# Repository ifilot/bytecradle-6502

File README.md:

# ByteCradle 6502

The **ByteCradle 6502** is a **single-board computer (SBC)** platform designed
for understanding and experimenting with **simple operating systems** on **8-bit
hardware**. Built around the **WDC 65C02** microprocessor, it provides a
hands-on platform for studying **system initialization, memory management,
device interfacing, and file system handling**.

> [!NOTE]  
> The source code for the ByteCradle 6502 operating system for the Mini is found
> in [a separate repository](https://github.com/ifilot/bytecradle-6502-operating-system).

## 📋 Table of Contents

- [BYTECRADLE 6502](#bytecradle-6502)
- [Overview](#overview)
  - [Shared Components](#shared-components)
- [Tier Comparison](#tier-comparison)
- [Obtaining PCBs](#obtaining-pcbs)
- [Download ROMs](#download-roms)
- [License](#license)
  - [Software](#software)
  - [Hardware](#hardware)
- [Contributing](#contributing)
- [Acknowledgements](#acknowledgements)

## Overview

Both SBCs share a common design philosophy — to provide a straightforward and
accessible 65C02 system, while exploring different levels of hardware
capability.

### Shared Components

- **CPU**: WDC 65C02
- **I/O**: WDC 65C51 Asynchronous Communications Interface Adapter (ACIA)

## Tier Comparison

This project offers two tiers of single board computers (SBCs), each tailored to
different levels of complexity and expandability:

- **Tiny SBC** (top): A simple, compact design ideal for learning or small
  embedded projects.
- **Mini SBC** (bottom): A more capable version with bank switching, SD card
  storage, and an expansion bus using the 65C22 Versatile Interface Adapter
  (VIA).

| Feature              | Tiny SBC                          | Mini SBC                             |
|----------------------|-----------------------------------|--------------------------------------|
| **PCB**              | Two layer                         | Four layer                           |
| **RAM**              | 32 KiB                            | 512 KiB (bank switched)              |
| **ROM**              | 32 KiB                            | 512 KiB (bank switched)              |
| **Bank Switching**   | No                                | Yes - 64 x 8 Kib banks               |
| **SD Card Support**  | No                                | Yes - Using WDC 65C22 VIA            |
| **I/O Interface**    | WDC 65C51 ACIA                    | WDC 65C51 ACIA                       |
| **Expansion Options**| Exposes system bus                | Exposes system bus and VIA bus       |

## Obtaining PCBs

You can have the ByteCradle PCBs manufactured at any PCB fabrication service of
your choice. However, for convenience and ease of ordering, we recommend using
[PCBWay](https://www.pcbway.com).

The following links will take you directly to the shared projects on PCBWay, where you can order the boards:

- [Order the Mini Board from PCBWay](https://www.pcbway.com/project/shareproject/ByteCradle_6502_Mini_Board_becc5f96.html)
- [Order the Tiny Board from PCBWay](https://www.pcbway.com/project/shareproject/ByteCradle_6502_Tiny_Board_7606b02a.html)

> [!NOTE]  
> These links direct you to the official project pages for the Mini and Tiny
> Boards on PCBWay.

## Download ROMs

Below are the available ROM images for use with the ByteCradle single-board
computers. These ROMs can be flashed onto your device depending on the board you
are using.

- **[TinyROM](https://github.com/ifilot/bytecradle-6502/releases/download/tinyrom-latest/tinyrom.bin)**  
  A lightweight ROM designed specifically for the Tiny Board. Ideal for minimal
  setups, testing, or basic 6502 development.

> [!IMPORTANT]  
> Make sure to select the appropriate ROM for your board model. Flashing the
> incorrect ROM may result in system instability.

## License

### Software

All software (including ROM code, tools, and firmware) in this repository is
licensed under the [GNU General Public License v3.0](LICENSE-GPL).

This means:
- You are free to use, modify, and share the software.
- If you distribute modified versions, you must also release them under the GPLv3.

### Hardware

All hardware design files (schematics, PCB layouts, bills of materials, etc.)
are licensed under the [CERN Open Hardware License v2 - Weakly Reciprocal
(CERN-OHL-W)](LICENSE-HARDWARE).

This means:
- You may study, modify, manufacture, and distribute the hardware freely.
- If you distribute a modified version, you must share your changes under the
  same license.

## Contributing

Contributions, ideas, and improvements are always welcome. Open an issue or
submit a pull request to get involved!

## Acknowledgements

We gratefully acknowledge [PCBWay](https://www.pcbway.com/) for their generous
support in sponsoring the prototype PCB manufacturing of the Mini Board. Their
assistance helped accelerate the development and testing of the hardware, and we
appreciate their commitment to supporting open hardware projects.

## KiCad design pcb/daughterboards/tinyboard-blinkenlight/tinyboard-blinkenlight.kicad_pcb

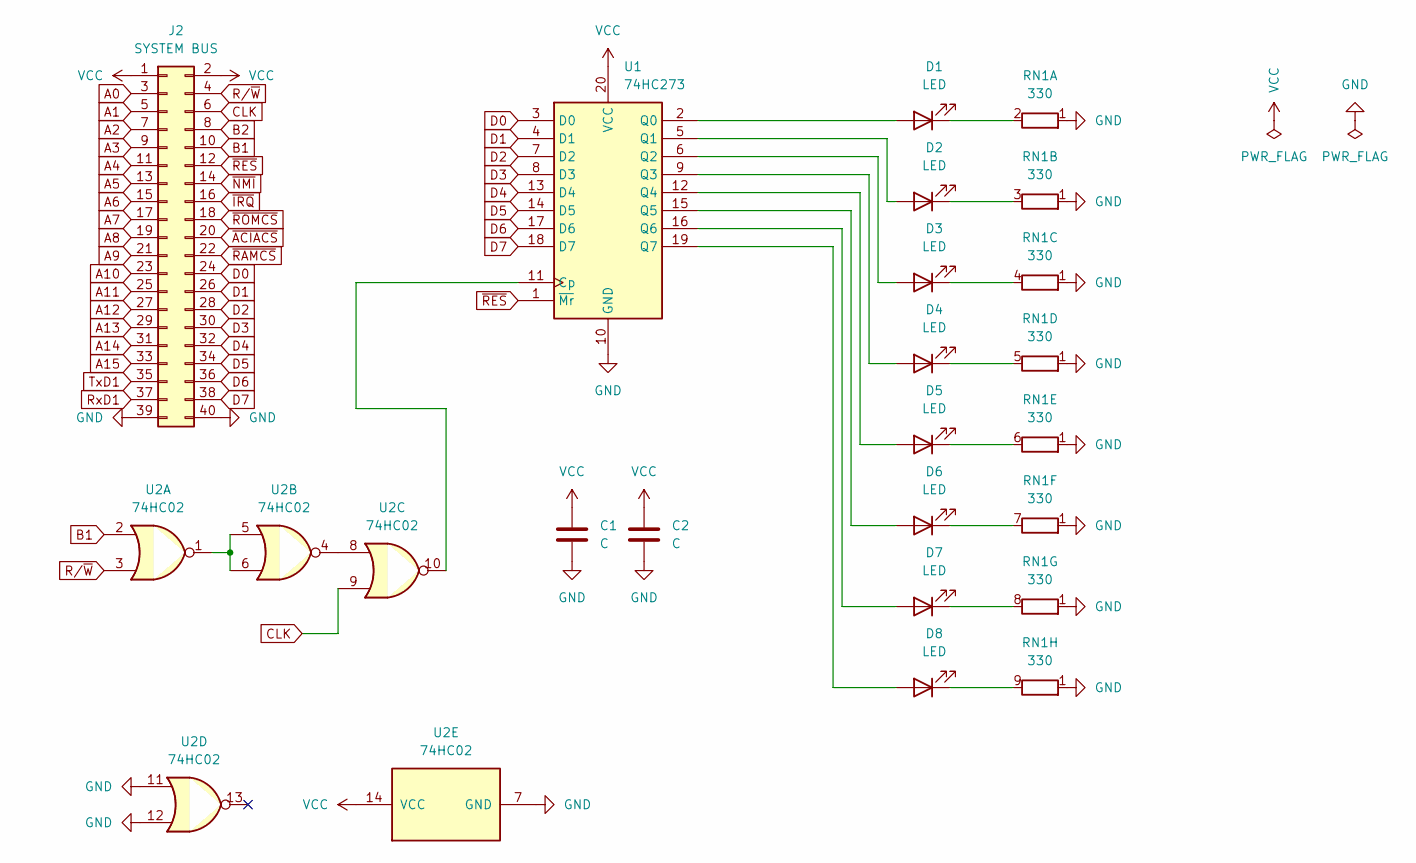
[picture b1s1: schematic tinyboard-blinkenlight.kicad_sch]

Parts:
C1, C2: C; C_Disc_D5.0mm_W2.5mm_P5.00mm
D1, D2, D3, D4, D5, D6, D7, D8: LED; LED_D5.0mm
J2: SYSTEM BUS; PinSocket_2x20_P2.54mm_Vertical
RN1: 330; R_Array_SIP9
U1: 74HC273; DIP-20_W7.62mm_Socket
U2: 74HC02; DIP-14_W7.62mm_Socket

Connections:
A0: J2.3
A1: J2.5
A2: J2.7
A3: J2.9
A4: J2.11
A5: J2.13
A6: J2.15
A7: J2.17
A8: J2.19
A9: J2.21
A10: J2.23
A11: J2.25
A12: J2.27
A13: J2.29
A14: J2.31
A15: J2.33
B1: J2.10, U2.2
B2: J2.8
CLK: J2.6, U2.9
D0: J2.24, U1.3 (D0)
D1: J2.26, U1.4 (D1)
D2: J2.28, U1.7 (D2)
D3: J2.30, U1.8 (D3)
D4: J2.32, U1.13 (D4)
D5: J2.34, U1.14 (D5)
D6: J2.36, U1.17 (D6)
D7: J2.38, U1.18 (D7)
GND: C1.2, C2.2, J2.39, J2.40, RN1.1 (R1), U1.10 (GND), U2.7 (GND), U2.11, U2.12
unnamed: D1.2 (A), U1.2 (Q0)
unnamed: D1.1 (K), RN1.2 (R1.2)
unnamed: D2.2 (A), U1.5 (Q1)
unnamed: D2.1 (K), RN1.3 (R2.2)
unnamed: D3.2 (A), U1.6 (Q2)
unnamed: D3.1 (K), RN1.4 (R3.2)
unnamed: D4.2 (A), U1.9 (Q3)
unnamed: D4.1 (K), RN1.5 (R4.2)
unnamed: D5.2 (A), U1.12 (Q4)
unnamed: D5.1 (K), RN1.6 (R5.2)
unnamed: D6.2 (A), U1.15 (Q5)
unnamed: D6.1 (K), RN1.7 (R6.2)
unnamed: D7.2 (A), U1.16 (Q6)
unnamed: D7.1 (K), RN1.8 (R7.2)
unnamed: D8.2 (A), U1.19 (Q7)
unnamed: D8.1 (K), RN1.9 (R8.2)
unnamed: U1.11 (Cp), U2.10
unnamed: U2.1, U2.5, U2.6
unnamed: U2.4, U2.8
RxD1: J2.37
R/~W: J2.4, U2.3
TxD1: J2.35
VCC: C1.1, C2.1, J2.1, J2.2, U1.20 (VCC), U2.14 (VCC)
~ACIACS: J2.20
~IRQ: J2.16
~NMI: J2.14
~RAMCS: J2.22
~RES: J2.12, U1.1 (~Mr)
~ROMCS: J2.18

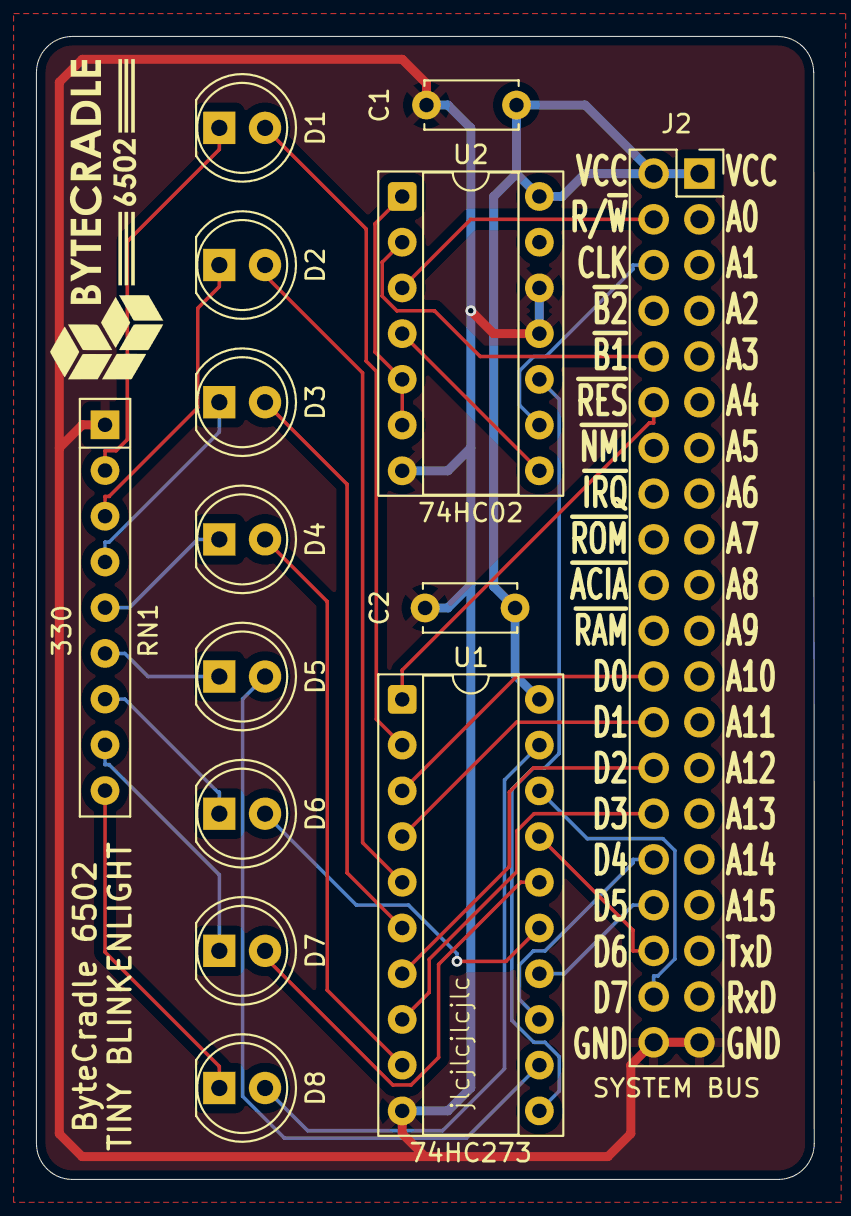
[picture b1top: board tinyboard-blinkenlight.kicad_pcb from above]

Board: 2 copper layers, 43.2 x 63.5 mm, 14 parts (0 on the bottom side), 33 nets.

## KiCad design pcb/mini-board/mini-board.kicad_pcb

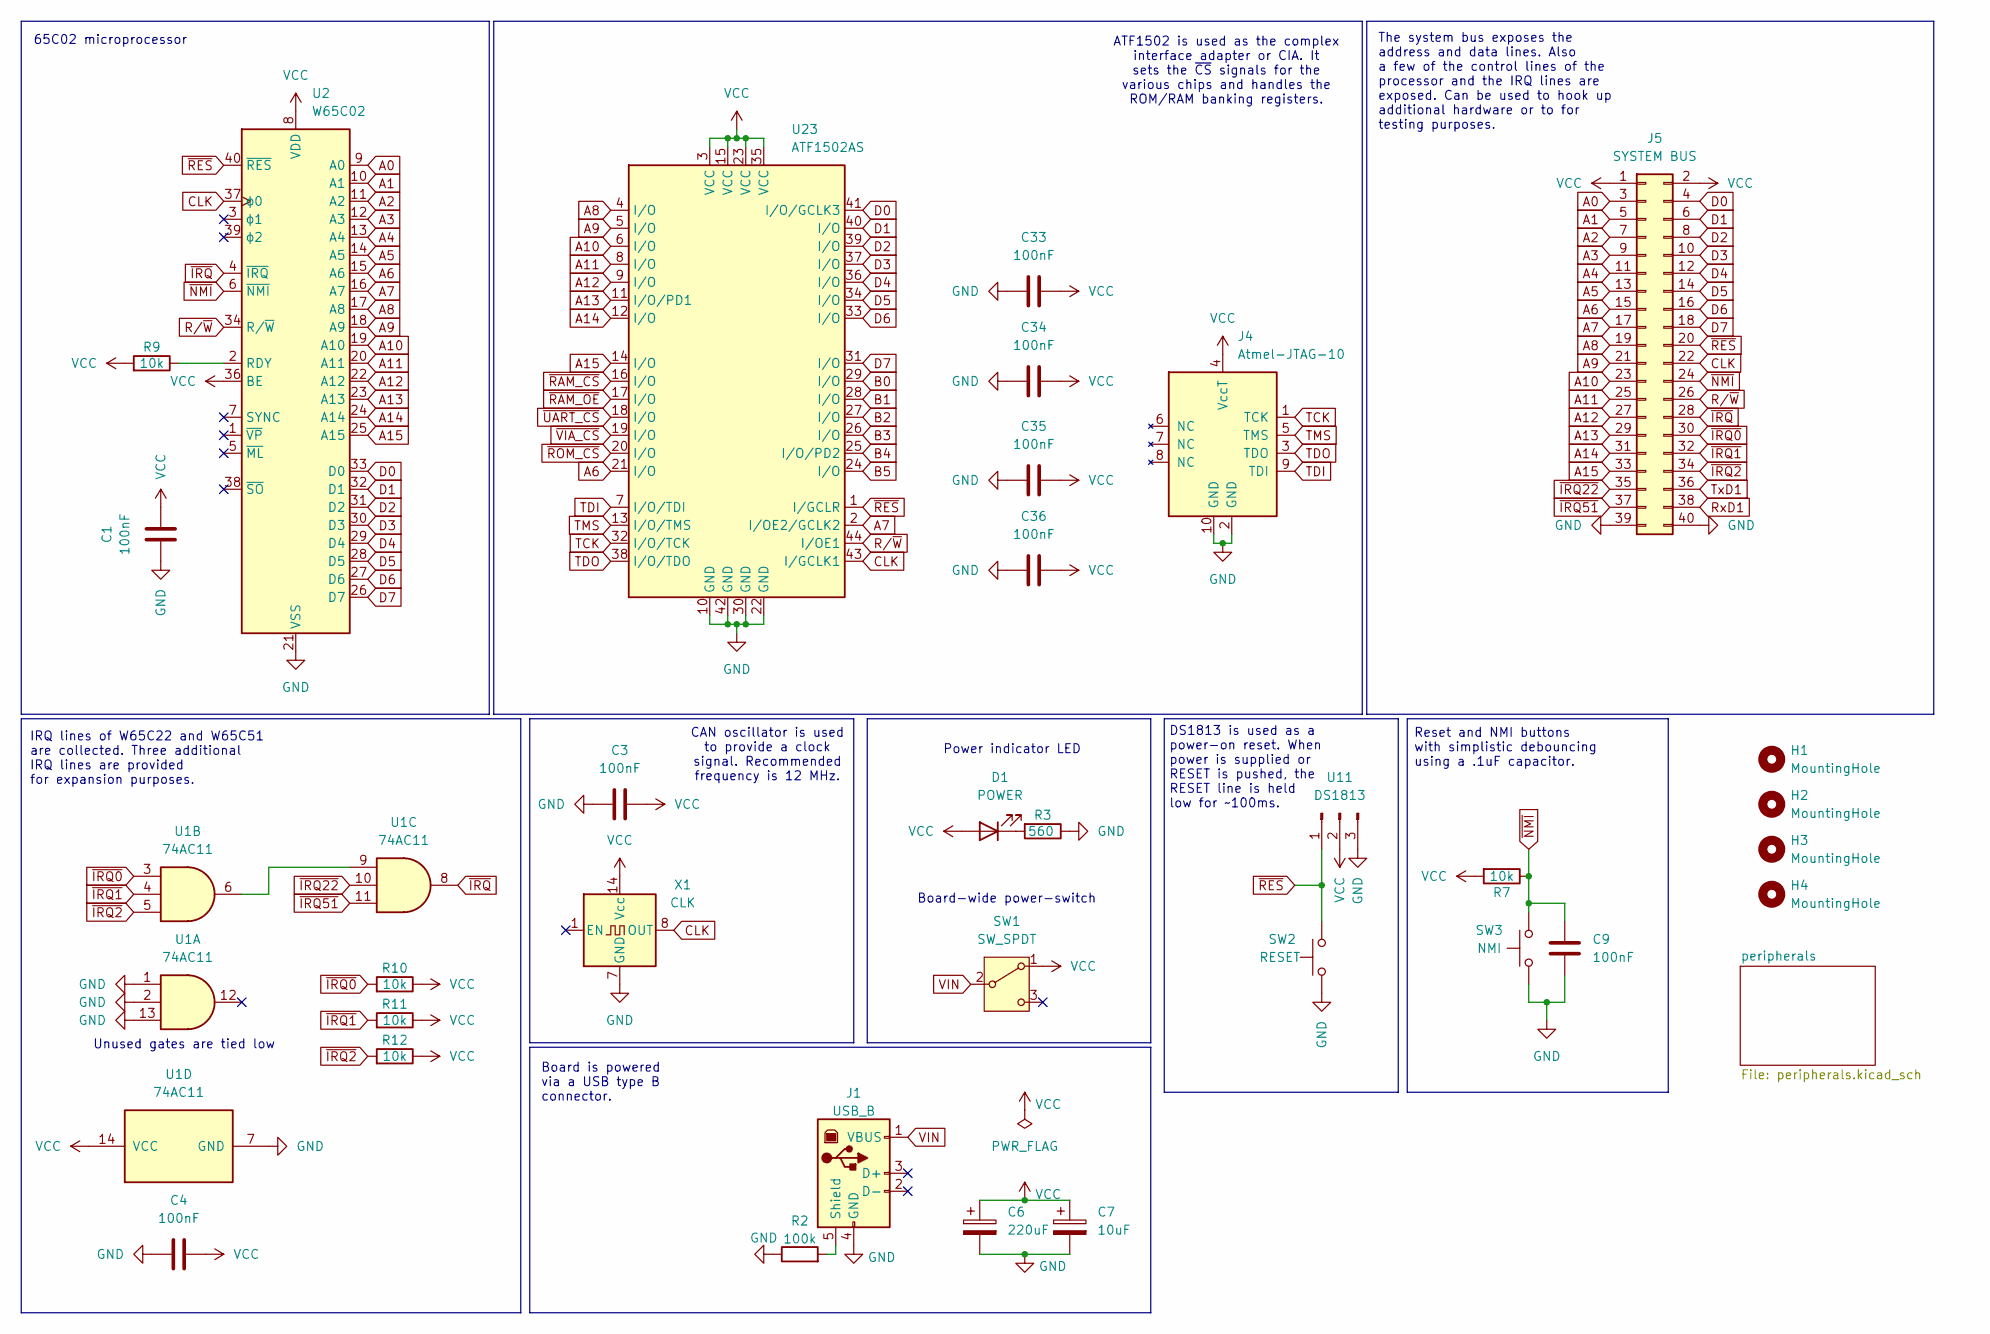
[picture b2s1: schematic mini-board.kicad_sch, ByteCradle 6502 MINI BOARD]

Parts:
C1, C3, C4, C9, C33, C34, C35, C36: 100nF; C_Disc_D5.0mm_W2.5mm_P5.00mm
C6: 220uF; CP_Radial_D6.3mm_P2.50mm
C7: 10uF; CP_Radial_D5.0mm_P2.50mm
D1: POWER; LED_D5.0mm
H1, H2, H3, H4: MountingHole; MountingHole_3.2mm_M3_DIN965_Pad_TopOnly
J1: USB_B; USB_B_OST_USB-B1HSxx_Horizontal
J4: Atmel-JTAG-10; IDC-Header_2x05_P2.54mm_Vertical
J5: SYSTEM BUS; PinHeader_2x20_P2.54mm_Vertical
R2: 100k; R_Axial_DIN0207_L6.3mm_D2.5mm_P7.62mm_Horizontal
R3: 560; R_Axial_DIN0207_L6.3mm_D2.5mm_P7.62mm_Horizontal
R7, R9, R10, R11, R12: 10k; R_Axial_DIN0207_L6.3mm_D2.5mm_P7.62mm_Horizontal
SW1: SW_SPDT; power_switch
SW2: RESET; SW_PUSH_6mm
SW3: NMI; SW_PUSH_6mm
U1: 74AC11; DIP-14_W7.62mm_Socket
U2: W65C02; DIP-40_W15.24mm_Socket
U11: DS1813; TO-92
U23: ATF1502AS; PLCC-44_THT-Socket
X1: CLK; Oscillator_DIP-14

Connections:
A0: J5.3, U2.9 (A0); also elsewhere on the board
A1: J5.5, U2.10 (A1); also elsewhere on the board
A2: J5.7, U2.11 (A2); also elsewhere on the board
A3: J5.9, U2.12 (A3); also elsewhere on the board
A4: J5.11, U2.13 (A4); also elsewhere on the board
A5: J5.13, U2.14 (A5); also elsewhere on the board
A6: J5.15, U2.15 (A6), U23.21 (I/O); also elsewhere on the board
A7: J5.17, U2.16 (A7), U23.2 (I/OE2/GCLK2); also elsewhere on the board
A8: J5.19, U2.17 (A8), U23.4 (I/O); also elsewhere on the board
A9: J5.21, U2.18 (A9), U23.5 (I/O); also elsewhere on the board
A10: J5.23, U2.19 (A10), U23.6 (I/O); also elsewhere on the board
A11: J5.25, U2.20 (A11), U23.8 (I/O); also elsewhere on the board
A12: J5.27, U2.22 (A12), U23.9 (I/O); also elsewhere on the board
A13: J5.29, U2.23 (A13), U23.11 (I/O/PD1)
A14: J5.31, U2.24 (A14), U23.12 (I/O)
A15: J5.33, U2.25 (A15), U23.14 (I/O)
B0: U23.29 (I/O); also elsewhere on the board
B1: U23.28 (I/O); also elsewhere on the board
B2: U23.27 (I/O); also elsewhere on the board
B3: U23.26 (I/O); also elsewhere on the board
B4: U23.25 (I/O/PD2); also elsewhere on the board
B5: U23.24 (I/O); also elsewhere on the board
CLK: J5.22, U2.37 (ϕ0), U23.43 (I/GCLK1), X1.8 (OUT); also elsewhere on the board
D0: J5.4, U2.33 (D0), U23.41 (I/O/GCLK3); also elsewhere on the board
D1: J5.6, U2.32 (D1), U23.40 (I/O); also elsewhere on the board
D2: J5.8, U2.31 (D2), U23.39 (I/O); also elsewhere on the board
D3: J5.10, U2.30 (D3), U23.37 (I/O); also elsewhere on the board
D4: J5.12, U2.29 (D4), U23.36 (I/O); also elsewhere on the board
D5: J5.14, U2.28 (D5), U23.34 (I/O); also elsewhere on the board
D6: J5.16, U2.27 (D6), U23.33 (I/O); also elsewhere on the board
D7: J5.18, U2.26 (D7), U23.31 (I/O); also elsewhere on the board
GND: C1.2, C3.2, C4.2, C6.2, C7.2, C9.2, C33.2, C34.2, C35.2, C36.2, J1.4 (GND), J4.2 (GND), J4.10 (GND), J5.39, J5.40, R2.1, R3.1, SW2.1, SW3.1, U1.1, U1.2, U1.7 (GND), U1.13, U2.21 (VSS), U11.3, U23.10 (GND), U23.22 (GND), U23.30 (GND), U23.42 (GND), X1.7 (GND); also elsewhere on the board
unnamed: D1.1 (K), R3.2
unnamed: J1.5 (Shield), R2.2
unnamed: U1.6, U1.9
unnamed: R9.1, U2.2 (RDY)
RxD1: J5.38; also elsewhere on the board
R/~W: J5.26, U2.34 (R/~W), U23.44 (I/OE1); also elsewhere on the board
TCK: J4.1 (TCK), U23.32 (I/O/TCK)
TDI: J4.9 (TDI), U23.7 (I/O/TDI)
TDO: J4.3 (TDO), U23.38 (I/O/TDO)
TMS: J4.5 (TMS), U23.13 (I/O/TMS)
TxD1: J5.36; also elsewhere on the board
VCC: C1.1, C3.1, C4.1, C6.1, C7.1, C33.1, C34.1, C35.1, C36.1, D1.2 (A), J4.4 (VccT), J5.1, J5.2, R7.2, R9.2, R10.1, R11.1, R12.1, SW1.1 (A), U1.14 (VCC), U2.8 (VDD), U2.36 (BE), U11.2, U23.3 (VCC), U23.15 (VCC), U23.23 (VCC), U23.35 (VCC), X1.14 (Vcc); also elsewhere on the board
VIN: J1.1 (VBUS), SW1.2 (B)
~IRQ0: J5.30, R10.2, U1.3
~IRQ1: J5.32, R11.2, U1.4
~IRQ2: J5.34, R12.2, U1.5
~IRQ22: J5.35, U1.10; also elsewhere on the board
~IRQ51: J5.37, U1.11; also elsewhere on the board
~IRQ: J5.28, U1.8, U2.4 (~IRQ)
~NMI: C9.1, J5.24, R7.1, SW3.2, U2.6 (~NMI); also elsewhere on the board
~RAM_CS: U23.16 (I/O); also elsewhere on the board
~RAM_OE: U23.17 (I/O); also elsewhere on the board
~RES: J5.20, SW2.2, U2.40 (~RES), U11.1, U23.1 (I/GCLR); also elsewhere on the board
~ROM_CS: U23.20 (I/O); also elsewhere on the board
~UART_CS: U23.18 (I/O); also elsewhere on the board
~VIA_CS: U23.19 (I/O); also elsewhere on the board

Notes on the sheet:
ATF1502 is used as the complex interface adapter or CIA. It sets the ~{CS} signals for the various chips and handles the ROM/RAM banking registers.
DS1813 is used as a power-on reset. When power is supplied or RESET is pushed, the RESET line is held low for ~100ms.
65C02 microprocessor
IRQ lines of W65C22 and W65C51 are collected. Three additional IRQ lines are provided for expansion purposes.
Reset and NMI buttons with simplistic debouncing using a .1uF capacitor.
Power indicator LED
The system bus exposes the address and data lines. Also a few of the control lines of the processor and the IRQ lines are exposed. Can be used to hook up additional hardware or to for testing purposes.
Unused gates are tied low
CAN oscillator is used to provide a clock signal. Recommended frequency is 12 MHz.
Board is powered via a USB type B connector.
Board-wide power-switch

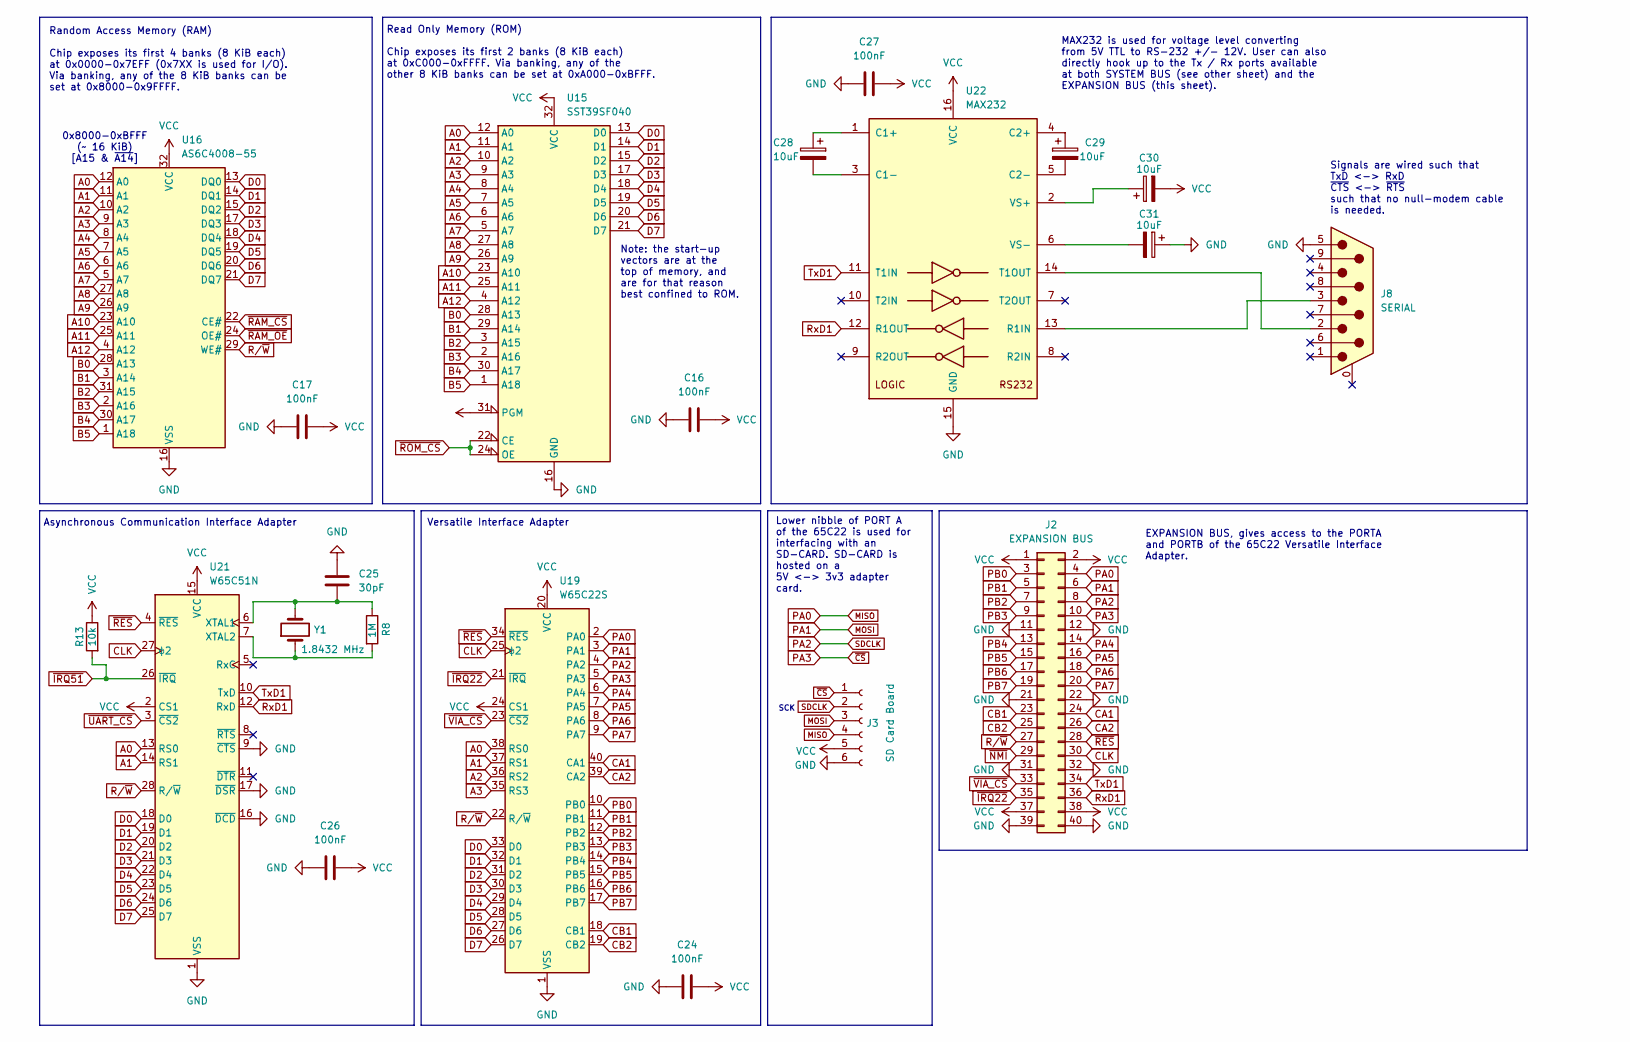
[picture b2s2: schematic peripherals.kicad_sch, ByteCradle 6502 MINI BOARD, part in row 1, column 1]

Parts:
C16, C17, C24, C26, C27: 100nF; C_Disc_D5.0mm_W2.5mm_P5.00mm
C25: 30pF; C_Disc_D5.0mm_W2.5mm_P5.00mm
C28, C29, C30, C31: 10uF; CP_Radial_D5.0mm_P2.50mm
J2: EXPANSION BUS; PinHeader_2x20_P2.54mm_Vertical
J3: SD Card Board; sdcard-socket
J8: SERIAL; DSUB-9_Pins_Horizontal_P2.77x2.84mm_EdgePinOffset4.94mm_Hou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
R8: 1M; R_Axial_DIN0207_L6.3mm_D2.5mm_P7.62mm_Horizontal
R13: 10k; R_Axial_DIN0207_L6.3mm_D2.5mm_P7.62mm_Horizontal
U15: SST39SF040; DIP-32_W15.24mm_Socket
U16: AS6C4008-55; DIP-32_W15.24mm_Socket
U19: W65C22S; DIP-40_W15.24mm_Socket
U21: W65C51N; DIP-28_W15.24mm_Socket
U22: MAX232; DIP-16_W7.62mm_Socket
Y1: 1.8432 MHz; Crystal_HC50_Vertical

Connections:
A0: U15.12 (A0), U16.12 (A0), U19.38 (RS0), U21.13 (RS0); also elsewhere on the board
A1: U15.11 (A1), U16.11 (A1), U19.37 (RS1), U21.14 (RS1); also elsewhere on the board
A2: U15.10 (A2), U16.10 (A2), U19.36 (RS2); also elsewhere on the board
A3: U15.9 (A3), U16.9 (A3), U19.35 (RS3); also elsewhere on the board
A4: U15.8 (A4), U16.8 (A4); also elsewhere on the board
A5: U15.7 (A5), U16.7 (A5); also elsewhere on the board
A6: U15.6 (A6), U16.6 (A6); also elsewhere on the board
A7: U15.5 (A7), U16.5 (A7); also elsewhere on the board
A8: U15.27 (A8), U16.27 (A8); also elsewhere on the board
A9: U15.26 (A9), U16.26 (A9); also elsewhere on the board
A10: U15.23 (A10), U16.23 (A10); also elsewhere on the board
A11: U15.25 (A11), U16.25 (A11); also elsewhere on the board
A12: U15.4 (A12), U16.4 (A12); also elsewhere on the board
B0: U15.28 (A13), U16.28 (A13); also elsewhere on the board
B1: U15.29 (A14), U16.3 (A14); also elsewhere on the board
B2: U15.3 (A15), U16.31 (A15); also elsewhere on the board
B3: U15.2 (A16), U16.2 (A16); also elsewhere on the board
B4: U15.30 (A17), U16.30 (A17); also elsewhere on the board
B5: U15.1 (A18), U16.1 (A18); also elsewhere on the board
CA1: J2.24, U19.40 (CA1)
CA2: J2.26, U19.39 (CA2)
CB1: J2.23, U19.18 (CB1)
CB2: J2.25, U19.19 (CB2)
CLK: J2.30, U19.25 (ϕ2), U21.27 (ϕ2); also elsewhere on the board
D0: U15.13 (D0), U16.13 (DQ0), U19.33 (D0), U21.18 (D0); also elsewhere on the board
D1: U15.14 (D1), U16.14 (DQ1), U19.32 (D1), U21.19 (D1); also elsewhere on the board
D2: U15.15 (D2), U16.15 (DQ2), U19.31 (D2), U21.20 (D2); also elsewhere on the board
D3: U15.17 (D3), U16.17 (DQ3), U19.30 (D3), U21.21 (D3); also elsewhere on the board
D4: U15.18 (D4), U16.18 (DQ4), U19.29 (D4), U21.22 (D4); also elsewhere on the board
D5: U15.19 (D5), U16.19 (DQ5), U19.28 (D5), U21.23 (D5); also elsewhere on the board
D6: U15.20 (D6), U16.20 (DQ6), U19.27 (D6), U21.24 (D6); also elsewhere on the board
D7: U15.21 (D7), U16.21 (DQ7), U19.26 (D7), U21.25 (D7); also elsewhere on the board
GND: C16.2, C17.2, C24.2, C25.1, C26.2, C27.2, C31.1, J2.11, J2.12, J2.21, J2.22, J2.31, J2.32, J2.39, J2.40, J3.6, J8.5, U15.16 (GND), U16.16 (VSS), U19.1 (VSS), U21.1 (VSS), U21.9 (~CTS), U21.16 (~DCD), U21.17 (~DSR), U22.15 (GND); also elsewhere on the board
MISO: J2.4, J3.4, U19.2 (PA0)
MOSI: J2.6, J3.3, U19.3 (PA1)
unnamed: C25.2, R8.1, U21.6 (XTAL1), Y1.2
unnamed: R8.2, U21.7 (XTAL2), Y1.1
unnamed: C28.1, U22.1 (C1+)
unnamed: C28.2, U22.3 (C1-)
unnamed: C29.1, U22.4 (C2+)
unnamed: C29.2, U22.5 (C2-)
unnamed: J8.3, U22.13 (R1IN)
unnamed: J8.2, U22.14 (T1OUT)
unnamed: C30.1, U22.2 (VS+)
unnamed: C31.2, U22.6 (VS-)
PA2: J2.8, J3.2, U19.4 (PA2)
PA3: J2.10, J3.1, U19.5 (PA3)
PA4: J2.14, U19.6 (PA4)
PA5: J2.16, U19.7 (PA5)
PA6: J2.18, U19.8 (PA6)
PA7: J2.20, U19.9 (PA7)
PB0: J2.3, U19.10 (PB0)
PB1: J2.5, U19.11 (PB1)
PB2: J2.7, U19.12 (PB2)
PB3: J2.9, U19.13 (PB3)
PB4: J2.13, U19.14 (PB4)
PB5: J2.15, U19.15 (PB5)
PB6: J2.17, U19.16 (PB6)
PB7: J2.19, U19.17 (PB7)
RxD1: J2.36, U21.12 (RxD), U22.12 (R1OUT); also elsewhere on the board
R/~W: J2.27, U16.29 (WE#), U19.22 (R/~W), U21.28 (R/~W); also elsewhere on the board
TxD1: J2.34, U21.10 (TxD), U22.11 (T1IN); also elsewhere on the board
VCC: C16.1, C17.1, C24.1, C26.1, C27.1, C30.2, J2.1, J2.2, J2.37, J2.38, J3.5, R13.1, U15.31 (PGM), U15.32 (VCC), U16.32 (VCC), U19.20 (VCC), U19.24 (CS1), U21.2 (CS1), U21.15 (VCC), U22.16 (VCC); also elsewhere on the board
~IRQ22: J2.35, U19.21 (~IRQ); also elsewhere on the board
~IRQ51: R13.2, U21.26 (~IRQ); also elsewhere on the board
~NMI: J2.29; also elsewhere on the board
~RAM_CS: U16.22 (CE#); also elsewhere on the board
~RAM_OE: U16.24 (OE#); also elsewhere on the board
~RES: J2.28, U19.34 (~RES), U21.4 (~RES); also elsewhere on the board
~ROM_CS: U15.22 (CE), U15.24 (OE); also elsewhere on the board
~UART_CS: U21.3 (~CS2); also elsewhere on the board
~VIA_CS: J2.33, U19.23 (~CS2); also elsewhere on the board

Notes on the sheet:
0x8000-0xBFFF (~ 16 KiB) [A15 & ~{A14}]
SCK
MAX232 is used for voltage level converting from 5V TTL to RS-232 +/- 12V. User can also directly hook up to the Tx / Rx ports available at both SYSTEM BUS (see other sheet) and the EXPANSION BUS (this sheet).
Signals are wired such that TxD <-> RxD ~{CTS} <-> ~{RTS} such that no null-modem cable is needed.
Versatile Interface Adapter
EXPANSION BUS, gives access to the PORTA and PORTB of the 65C22 Versatile Interface Adapter.
Asynchronous Communication Interface Adapter
Lower nibble of PORT A of the 65C22 is used for interfacing with an SD-CARD. SD-CARD is hosted on a 5V <-> 3v3 adapter card.
Note: the start-up vectors are at the top of memory, and are for that reason best confined to ROM.
Read Only Memory (ROM) Chip exposes its first 2 banks (8 KiB each) at 0xC000-0xFFFF. Via banking, any of the other 8 KiB banks can be set at 0xA000-0xBFFF.
Random Access Memory (RAM) Chip exposes its first 4 banks (8 KiB each) at 0x0000-0x7EFF (0x7XX is used for I/O). Via banking, any of the 8 KiB banks can be set at 0x8000-0x9FFFF.

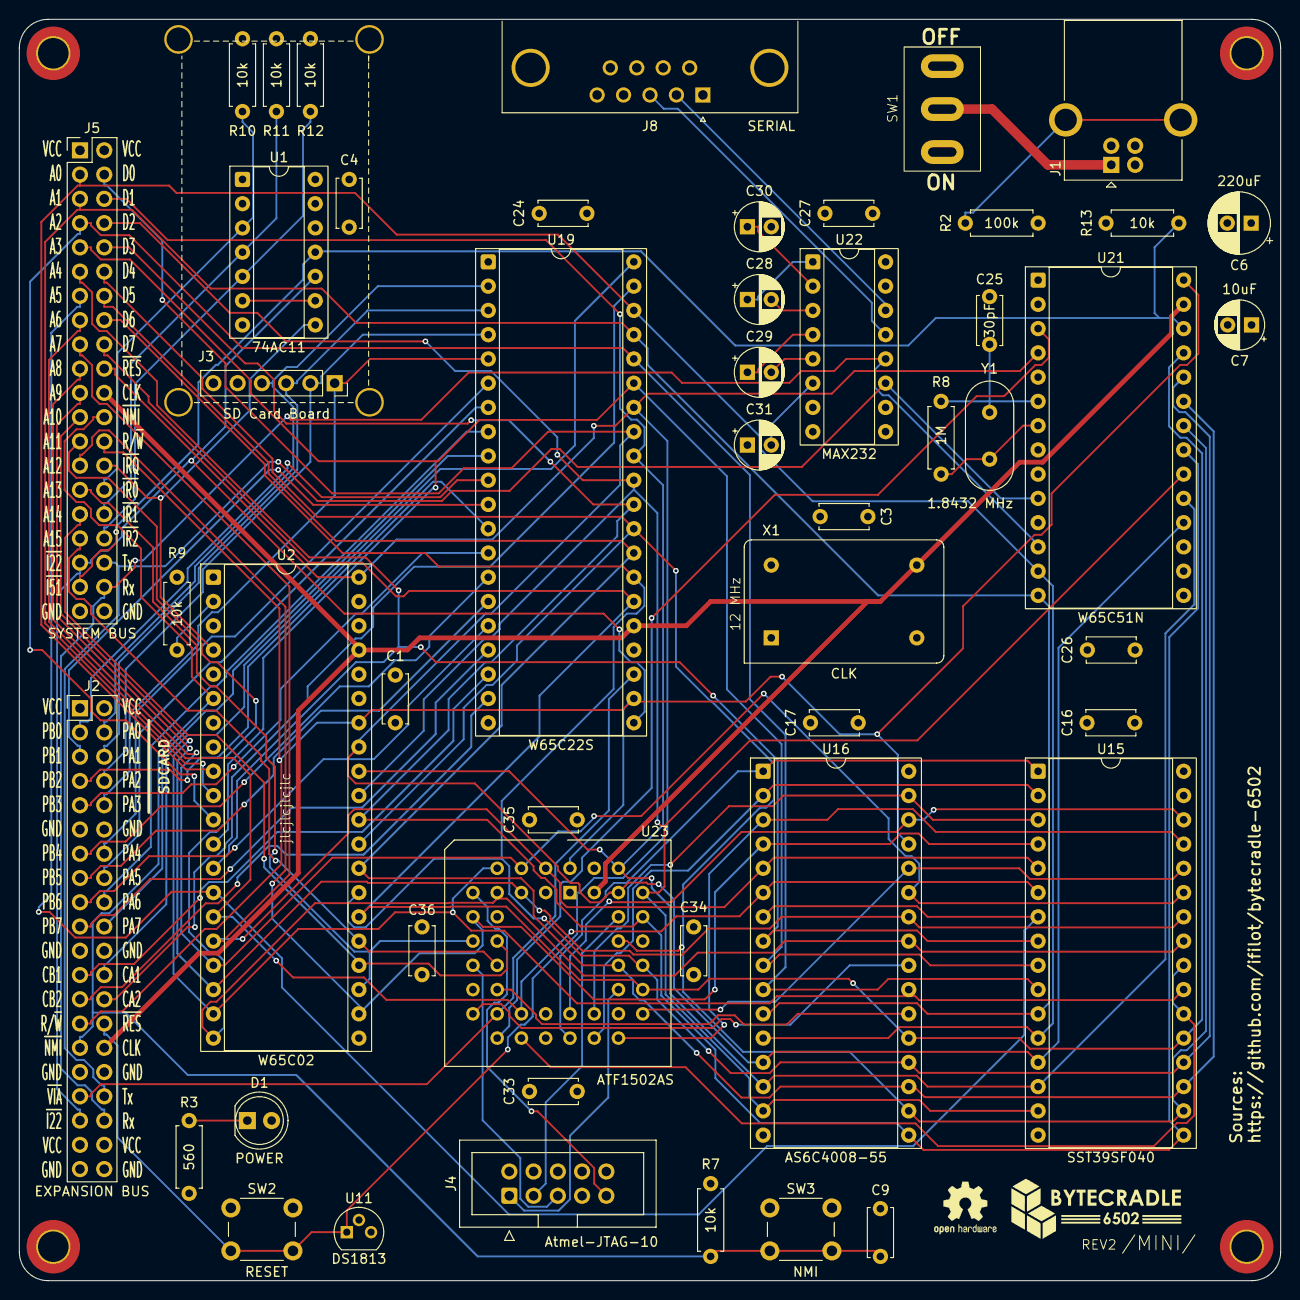
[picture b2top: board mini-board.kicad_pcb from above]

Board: 4 copper layers, 132.1 x 132.1 mm, 56 parts (0 on the bottom side), 88 nets.

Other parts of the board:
G001: LOGO; bytecradle-logo
G002: OSHW-Logo2_7.3x6mm_SilkScreen

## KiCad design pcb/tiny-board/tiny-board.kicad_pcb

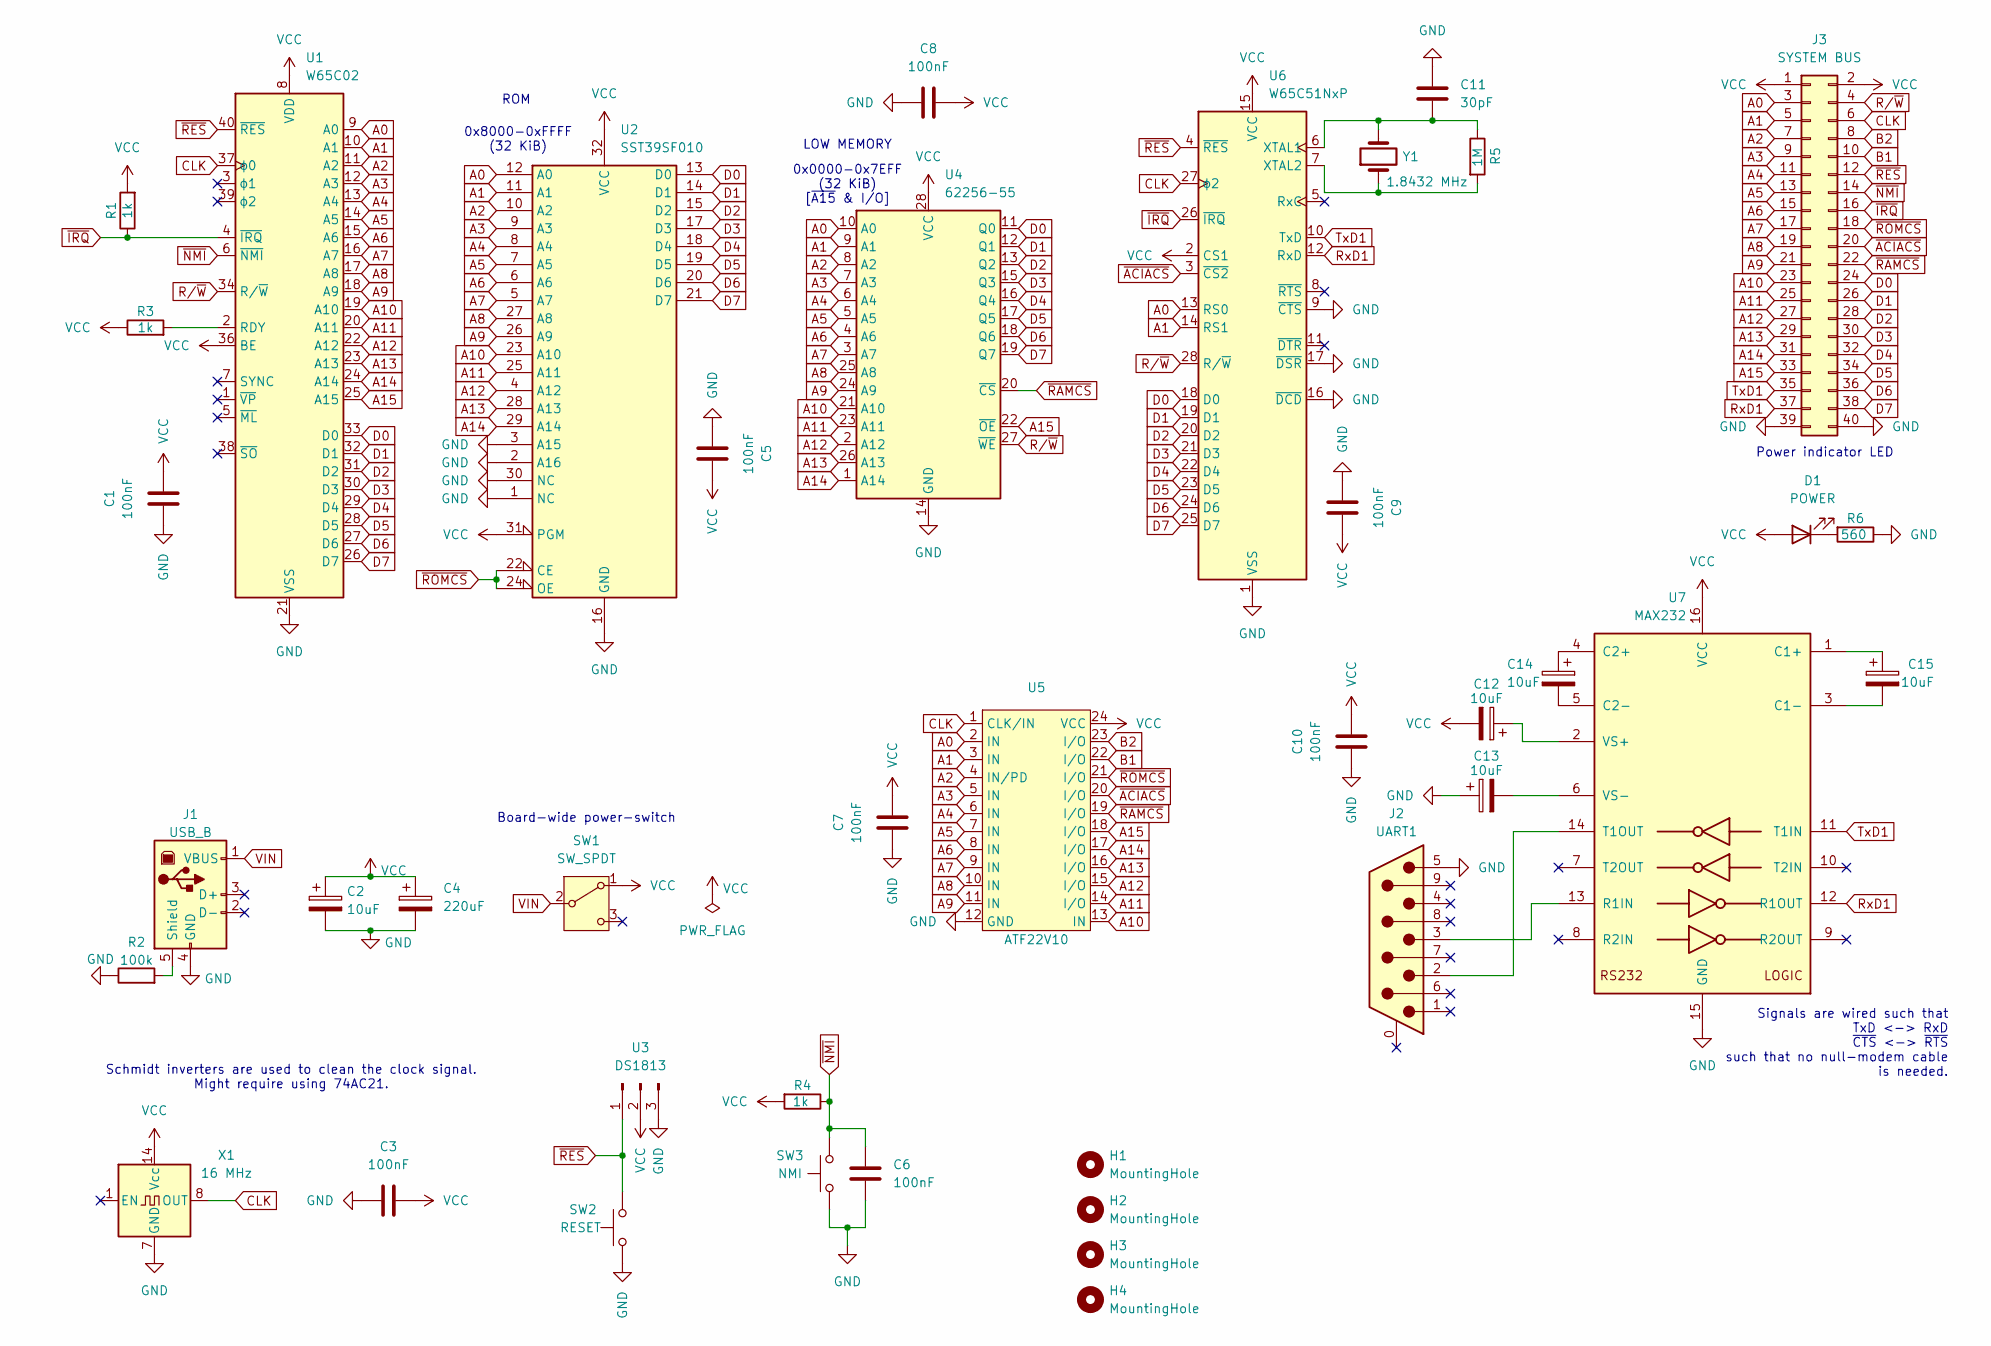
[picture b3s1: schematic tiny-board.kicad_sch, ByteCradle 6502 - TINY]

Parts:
C1, C3, C5, C6, C7, C8, C9, C10: 100nF; C_Disc_D5.0mm_W2.5mm_P5.00mm
C2, C12, C13, C14, C15: 10uF; CP_Radial_D5.0mm_P2.50mm
C4: 220uF; CP_Radial_D6.3mm_P2.50mm
C11: 30pF; C_Disc_D5.0mm_W2.5mm_P5.00mm
D1: POWER; LED_D5.0mm
H1, H2, H3, H4: MountingHole; MountingHole_3.2mm_M3_DIN965_Pad_TopOnly
J1: USB_B; USB_B_OST_USB-B1HSxx_Horizontal
J2: UART1; DSUB-9_Pins_Horizontal_P2.77x2.84mm_EdgePinOffset4.94mm_Hou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
J3: SYSTEM BUS; PinHeader_2x20_P2.54mm_Vertical
R1, R3, R4: 1k; R_Axial_DIN0207_L6.3mm_D2.5mm_P7.62mm_Horizontal
R2: 100k; R_Axial_DIN0207_L6.3mm_D2.5mm_P7.62mm_Horizontal
R5: 1M; R_Axial_DIN0207_L6.3mm_D2.5mm_P7.62mm_Horizontal
R6: 560; R_Axial_DIN0207_L6.3mm_D2.5mm_P7.62mm_Horizontal
SW1: SW_SPDT; power_switch
SW2: RESET; SW_PUSH_6mm
SW3: NMI; SW_PUSH_6mm
U1: W65C02; DIP-40_W15.24mm_Socket
U2: SST39SF010; DIP-32_W15.24mm_Socket
U3: DS1813; TO-92
U4: 62256-55; DIP-28_W15.24mm_Socket
U5: ATF22V10; DIP-24_W7.62mm_Socket
U6: W65C51NxP; DIP-28_W15.24mm_Socket
U7: MAX232; DIP-16_W7.62mm_Socket
X1: 16 MHz; Oscillator_DIP-14
Y1: 1.8432 MHz; Crystal_HC50_Vertical

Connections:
A0: J3.3, U1.9 (A0), U2.12 (A0), U4.10 (A0), U5.2 (IN), U6.13 (RS0)
A1: J3.5, U1.10 (A1), U2.11 (A1), U4.9 (A1), U5.3 (IN), U6.14 (RS1)
A2: J3.7, U1.11 (A2), U2.10 (A2), U4.8 (A2), U5.4 (IN/PD)
A3: J3.9, U1.12 (A3), U2.9 (A3), U4.7 (A3), U5.5 (IN)
A4: J3.11, U1.13 (A4), U2.8 (A4), U4.6 (A4), U5.6 (IN)
A5: J3.13, U1.14 (A5), U2.7 (A5), U4.5 (A5), U5.7 (IN)
A6: J3.15, U1.15 (A6), U2.6 (A6), U4.4 (A6), U5.8 (IN)
A7: J3.17, U1.16 (A7), U2.5 (A7), U4.3 (A7), U5.9 (IN)
A8: J3.19, U1.17 (A8), U2.27 (A8), U4.25 (A8), U5.10 (IN)
A9: J3.21, U1.18 (A9), U2.26 (A9), U4.24 (A9), U5.11 (IN)
A10: J3.23, U1.19 (A10), U2.23 (A10), U4.21 (A10), U5.13 (IN)
A11: J3.25, U1.20 (A11), U2.25 (A11), U4.23 (A11), U5.14 (I/O)
A12: J3.27, U1.22 (A12), U2.4 (A12), U4.2 (A12), U5.15 (I/O)
A13: J3.29, U1.23 (A13), U2.28 (A13), U4.26 (A13), U5.16 (I/O)
A14: J3.31, U1.24 (A14), U2.29 (A14), U4.1 (A14), U5.17 (I/O)
A15: J3.33, U1.25 (A15), U4.22 (~OE), U5.18 (I/O)
B1: J3.10, U5.22 (I/O)
B2: J3.8, U5.23 (I/O)
CLK: J3.6, U1.37 (ϕ0), U5.1 (CLK/IN), U6.27 (ϕ2), X1.8 (OUT)
D0: J3.24, U1.33 (D0), U2.13 (D0), U4.11 (Q0), U6.18 (D0)
D1: J3.26, U1.32 (D1), U2.14 (D1), U4.12 (Q1), U6.19 (D1)
D2: J3.28, U1.31 (D2), U2.15 (D2), U4.13 (Q2), U6.20 (D2)
D3: J3.30, U1.30 (D3), U2.17 (D3), U4.15 (Q3), U6.21 (D3)
D4: J3.32, U1.29 (D4), U2.18 (D4), U4.16 (Q4), U6.22 (D4)
D5: J3.34, U1.28 (D5), U2.19 (D5), U4.17 (Q5), U6.23 (D5)
D6: J3.36, U1.27 (D6), U2.20 (D6), U4.18 (Q6), U6.24 (D6)
D7: J3.38, U1.26 (D7), U2.21 (D7), U4.19 (Q7), U6.25 (D7)
GND: C1.2, C2.2, C3.2, C4.2, C5.2, C6.2, C7.2, C8.2, C9.2, C10.2, C11.1, C13.1, J1.4 (GND), J2.5, J3.39, J3.40, R2.1, R6.1, SW2.1, SW3.1, U1.21 (VSS), U2.1 (NC), U2.2 (A16), U2.3 (A15), U2.16 (GND), U2.30 (NC), U3.3, U4.14 (GND), U5.12 (GND), U6.1 (VSS), U6.9 (~CTS), U6.16 (~DCD), U6.17 (~DSR), U7.15 (GND), X1.7 (GND)
unnamed: D1.1 (K), R6.2
unnamed: J1.5 (Shield), R2.2
unnamed: R3.2, U1.2 (RDY)
unnamed: C11.2, R5.1, U6.6 (XTAL1), Y1.2
unnamed: R5.2, U6.7 (XTAL2), Y1.1
unnamed: C15.1, U7.1 (C1+)
unnamed: C15.2, U7.3 (C1-)
unnamed: C14.1, U7.4 (C2+)
unnamed: C14.2, U7.5 (C2-)
unnamed: J2.3, U7.13 (R1IN)
unnamed: J2.2, U7.14 (T1OUT)
unnamed: C12.1, U7.2 (VS+)
unnamed: C13.2, U7.6 (VS-)
RxD1: J3.37, U6.12 (RxD), U7.12 (R1OUT)
R/~W: J3.4, U1.34 (R/~W), U4.27 (~WE), U6.28 (R/~W)
TxD1: J3.35, U6.10 (TxD), U7.11 (T1IN)
VCC: C1.1, C2.1, C3.1, C4.1, C5.1, C7.1, C8.1, C9.1, C10.1, C12.2, D1.2 (A), J3.1, J3.2, R1.2, R3.1, R4.2, SW1.1 (A), U1.8 (VDD), U1.36 (BE), U2.31 (PGM), U2.32 (VCC), U3.2, U4.28 (VCC), U5.24 (VCC), U6.2 (CS1), U6.15 (VCC), U7.16 (VCC), X1.14 (Vcc)
VIN: J1.1 (VBUS), SW1.2 (B)
~ACIACS: J3.20, U5.20 (I/O), U6.3 (~CS2)
~IRQ: J3.16, R1.1, U1.4 (~IRQ), U6.26 (~IRQ)
~NMI: C6.1, J3.14, R4.1, SW3.2, U1.6 (~NMI)
~RAMCS: J3.22, U4.20 (~CS), U5.19 (I/O)
~RES: J3.12, SW2.2, U1.40 (~RES), U3.1, U6.4 (~RES)
~ROMCS: J3.18, U2.22 (CE), U2.24 (OE), U5.21 (I/O)

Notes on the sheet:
LOW MEMORY
0x0000-0x7EFF (32 KiB) [~{A15} & I/O]
0x8000-0xFFFF (32 KiB)
Schmidt inverters are used to clean the clock signal. Might require using 74AC21.
Power indicator LED
ROM
Signals are wired such that TxD <-> RxD ~{CTS} <-> ~{RTS} such that no null-modem cable is needed.
Board-wide power-switch
